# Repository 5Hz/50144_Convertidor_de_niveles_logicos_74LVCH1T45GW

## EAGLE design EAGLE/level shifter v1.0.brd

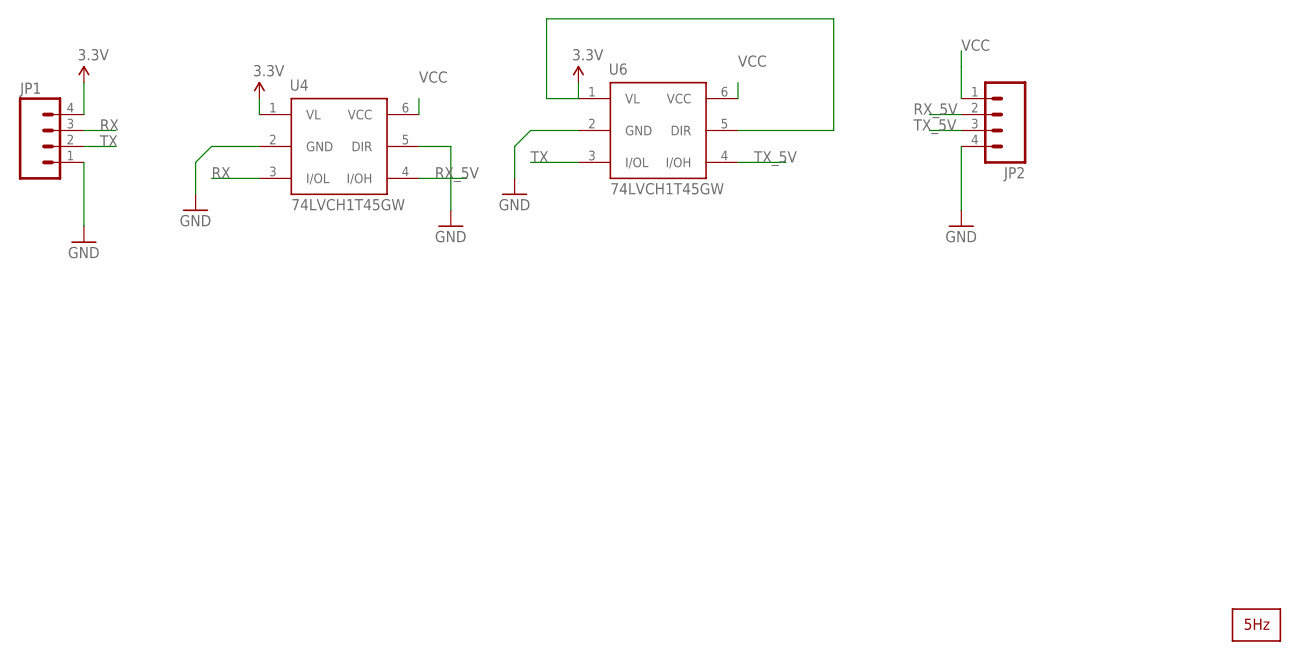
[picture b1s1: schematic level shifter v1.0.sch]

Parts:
JP1, JP2: M04PTH; 1X04
U4, U6: 74LVCH1T45GW; SOT-363
U$1: LOGO_COPPER5MM; LOGO_COP_5MM

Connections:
3.3V: JP1.4, U4.1 (VL), U6.1 (VL), U6.5 (DIR)
GND: JP1.1, JP2.4, U4.2 (GND), U4.5 (DIR), U6.2 (GND)
RX: JP1.3, U4.3 (I/OL)
RX_5V: JP2.2, U4.4 (I/OH)
TX: JP1.2, U6.3 (I/OL)
TX_5V: JP2.3, U6.4 (I/OH)
VCC: JP2.1, U4.6 (VCC), U6.6 (VCC)

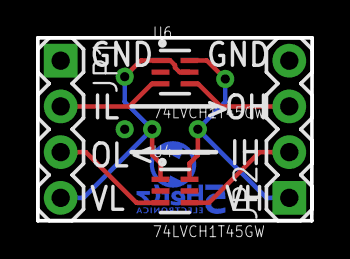
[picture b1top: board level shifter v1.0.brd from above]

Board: 2 copper layers, 15.2 x 10.2 mm, 5 parts (1 on the bottom side), 7 nets.

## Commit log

2014-03-20 Creación
